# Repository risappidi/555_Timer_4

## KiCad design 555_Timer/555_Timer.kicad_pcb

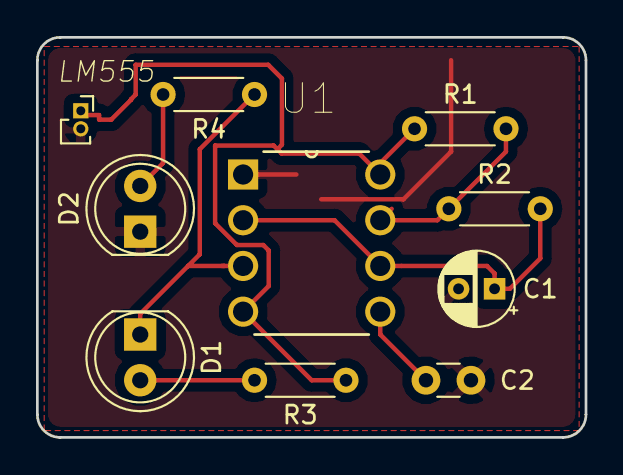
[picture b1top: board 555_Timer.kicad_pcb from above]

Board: 2 copper layers, 30.5 x 22.2 mm, 9 parts (0 on the bottom side), 8 nets.

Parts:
C1: CP; CP_Radial_D4.0mm_P2.00mm
C2: C; C_Disc_D3.0mm_W1.6mm_P2.50mm
D1, D2: LED_ALT; LED_D5.0mm_Clear
R1, R2, R3, R4: R; R_Axial_DIN0204_L3.6mm_D1.6mm_P5.08mm_Horizontal
U1: LM555; DIP254P762X533-8

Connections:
+5V: R1.1, R3.1, U1.4, U1.8
GND: C1.2, C2.2, D2.1, U1.1
unnamed: C1.1, R2.2, U1.2, U1.6
unnamed: C2.1, U1.5
unnamed: D1.1, R4.1, U1.3
unnamed: D1.2, R3.2
unnamed: D2.2, R4.2
unnamed: R1.2, R2.1, U1.7
